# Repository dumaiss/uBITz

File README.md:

# uBITz
**μBITz** – *ZAP 80s dreams into silicon.*   

Open modular 8-bit style system: host Z80/6502/68k/RISC-V, tile SID/POKEY, boot in '83.   M.2 LVDS serial, I²C map, Parity-10, ZAP IRQs.   Spec + KiCad + Verilog + ref impl.   Build. ZAP. Retro lives.   `ubitz.dev` #μBITz

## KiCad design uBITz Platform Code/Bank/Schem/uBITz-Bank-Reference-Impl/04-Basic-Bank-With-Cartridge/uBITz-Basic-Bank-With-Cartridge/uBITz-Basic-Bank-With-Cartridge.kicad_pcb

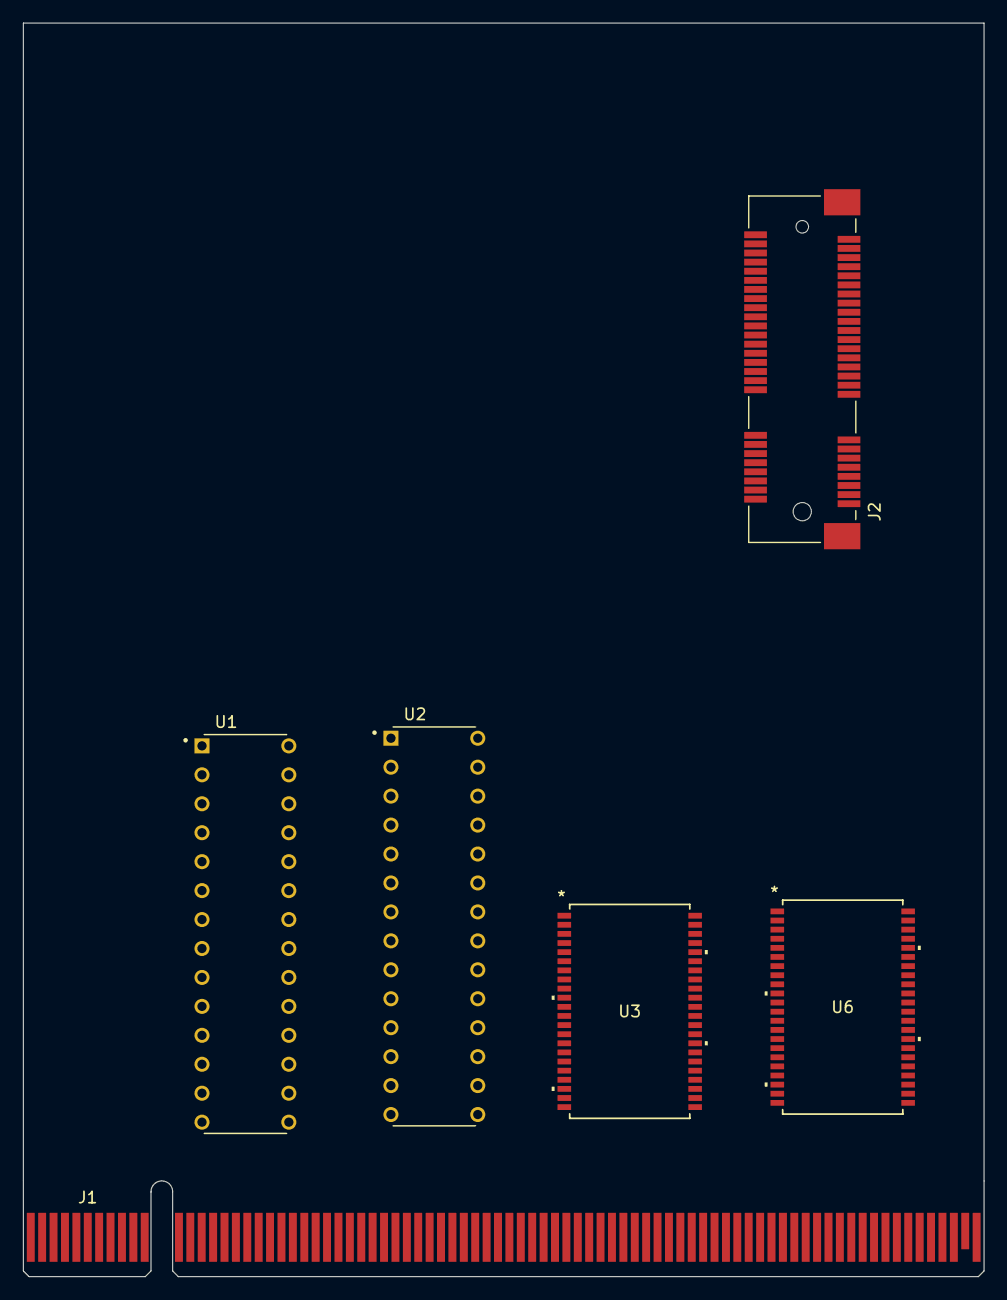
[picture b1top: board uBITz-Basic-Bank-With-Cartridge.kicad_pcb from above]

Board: 4 copper layers, 84.3 x 110.0 mm, 6 parts (0 on the bottom side), 37 nets, no tracks yet.

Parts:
J1: BUS_PCIexpress_x16
J2: uBITz-Bank-Cartridge; BUS_PCI_Express_Mini_Full
U1, U2: AT28C256-15PU; DIP762W48P254L3467H406Q28
U3, U6: AS7C34096A-10TIN; TSOP-44_18P52X11P94_ALL

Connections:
+5V: J1.A2 (+5V_MAIN), J1.A3 (+5V_MAIN), J1.B1 (+5V_MAIN), J1.B2 (+5V_MAIN), J1.B3 (+5V_MAIN), U1.28 (VCC), U2.28 (VCC), U3.11 (VCC), U3.33 (VCC), U6.11 (VCC), U6.33 (VCC)
/A0: J1.B14 (A0), U1.10 (A0), U2.10 (A0), U3.3 (A0), U6.3 (A0)
/A1: J1.B15 (A1), U1.9 (A1), U2.9 (A1), U3.4 (A1), U6.4 (A1)
/A2: J1.B17 (A2), U1.8 (A2), U2.8 (A2), U3.5 (A2), U6.5 (A2)
/A3: J1.B18 (A3), U1.7 (A3), U2.7 (A3), U3.6 (A3), U6.6 (A3)
/A4: J1.B19 (A4), U1.6 (A4), U2.6 (A4), U3.7 (A4), U6.7 (A4)
/A5: J1.B20 (A5), U1.5 (A5), U2.5 (A5), U3.16 (A5), U6.16 (A5)
/A6: J1.B23 (A6), U1.4 (A6), U2.4 (A6), U3.17 (A6), U6.17 (A6)
/A7: J1.B24 (A7), U1.3 (A7), U2.3 (A7), U3.18 (A7), U6.18 (A7)
/A8: J1.B27 (A8), U1.25 (A8), U2.25 (A8), U3.19 (A8), U6.19 (A8)
/A9: J1.B28 (A9), U1.24 (A9), U2.24 (A9), U3.20 (A9), U6.20 (A9)
/A10: J1.B30 (A10), U1.21 (A10), U2.21 (A10), U3.26 (A10), U6.26 (A10)
/A11: J1.B31 (A11), U1.23 (A11), U2.23 (A11), U3.27 (A11), U6.27 (A11)
/A12: J1.B33 (A12), U1.2 (A12), U2.2 (A12), U3.28 (A12), U6.28 (A12)
/A13: J1.B34 (A13), U1.26 (A13), U2.26 (A13), U3.29 (A13), U6.29 (A13)
/A14: J1.B37 (A14), U1.1 (A14), U2.1 (A14), U3.30 (A14), U6.30 (A14)
/A15: J1.B38 (A15), U3.38 (A15), U6.38 (A15)
/A16: J1.B41 (A16), U3.39 (A16), U6.39 (A16)
/A17: J1.B42 (A17), U3.40 (A17), U6.40 (A17)
/A18: J1.B45 (A18), U3.41 (A18), U6.41 (A18)
/D0: J1.A72 (D0), U2.11 (I/O0), U6.9 (I/O1)
/D1: J1.A69 (D1), U2.12 (I/O1), U6.10 (I/O2)
/D2: J1.A68 (D2), U2.13 (I/O2), U6.13 (I/O3)
/D3: J1.A65 (D3), U2.15 (I/O3), U6.14 (I/O4)
/D4: J1.A64 (D4), U2.19 (I/O7), U6.31 (I/O5)
/D5: J1.A61 (D5), U2.18 (I/O6), U6.32 (I/O6)
/D6: J1.A60 (D6), U2.17 (I/O5), U6.35 (I/O7)
/D7: J1.A57 (D7), U2.16 (I/O4), U6.36 (I/O8)
/D8: U1.11 (I/O0), U3.9 (I/O1)
/D9: U1.12 (I/O1), U3.10 (I/O2)
/D10: U1.13 (I/O2), U3.13 (I/O3)
/D11: U1.15 (I/O3), U3.14 (I/O4)
/D12: U1.19 (I/O7), U3.31 (I/O5)
/D13: U1.18 (I/O6), U3.32 (I/O6)
/D14: U1.17 (I/O5), U3.35 (I/O7)
/D15: U1.16 (I/O4), U3.36 (I/O8)
GND: J1.A1 (~DRV5V), J1.A4 (GND), J1.A5 (GND), J1.A6 (GND), J1.A11 (~SENS3V), J1.A12 (GND), J1.A15 (GND), J1.A18 (GND), J1.A23 (GND), J1.A24 (GND), J1.A27 (GND), J1.A28 (GND), J1.A30 (GND), J1.A34 (GND), J1.A37 (GND), J1.A38 (GND), J1.A41 (GND), J1.A42 (GND), J1.A45 (GND), J1.A46 (GND), J1.A50 (GND), J1.A51 (GND), J1.A54 (GND), J1.A55 (GND), J1.A58 (GND), J1.A59 (GND), J1.A62 (GND), J1.A63 (GND), J1.A66 (GND), J1.A67 (GND), J1.A70 (GND), J1.A71 (GND), J1.B4 (GND), J1.B7 (GND), J1.B8 (GND), J1.B11 (GND), J1.B13 (GND), J1.B16 (GND), J1.B21 (GND), J1.B22 (GND), J1.B25 (GND), J1.B26 (GND), J1.B29 (GND), J1.B32 (GND), J1.B35 (GND), J1.B36 (GND), J1.B39 (GND), J1.B40 (GND), J1.B43 (GND), J1.B44 (GND), J1.B47 (GND), J1.B48 (GND), J1.B52 (GND), J1.B53 (GND), J1.B56 (GND), J1.B57 (GND), J1.B60 (GND), J1.B61 (GND), J1.B64 (GND), J1.B65 (GND), J1.B68 (GND), J1.B69 (GND), J1.B72 (GND), U1.14 (GND), U2.14 (GND), U3.12 (GND), U3.34 (GND), U6.12 (GND), U6.34 (GND)

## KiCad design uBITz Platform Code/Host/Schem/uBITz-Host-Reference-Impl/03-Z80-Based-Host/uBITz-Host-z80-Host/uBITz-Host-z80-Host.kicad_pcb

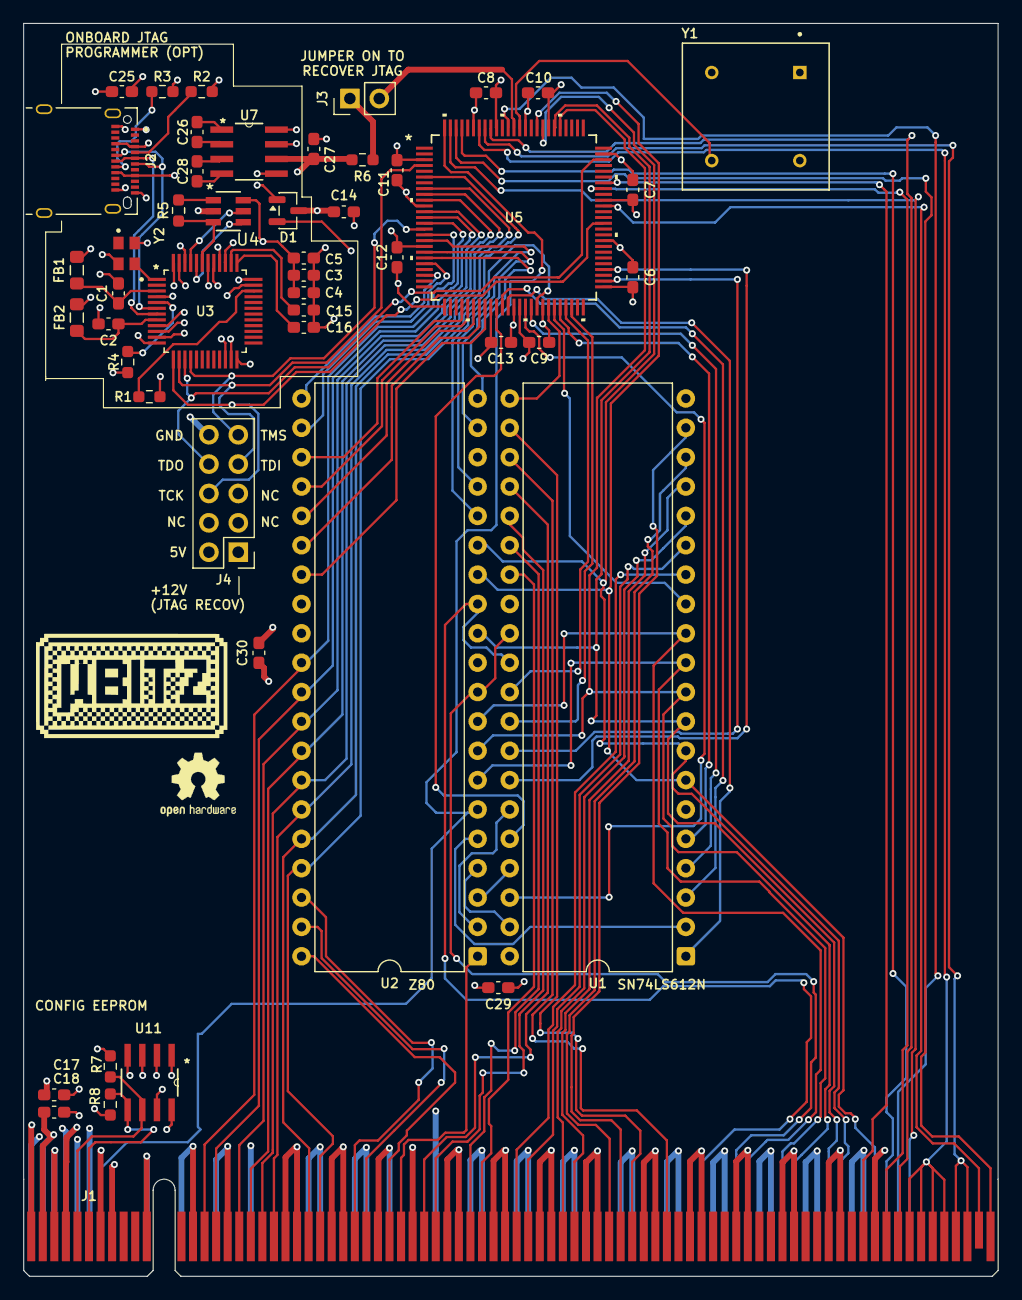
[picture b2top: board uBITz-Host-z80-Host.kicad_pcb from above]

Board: 4 copper layers, 84.3 x 108.4 mm, 48 parts (0 on the bottom side), 104 nets.

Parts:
C1, C2, C3, C14, C17, C18: 10u; C_0603_1608Metric_Pad1.08x0.95mm_HandSolder
C4, C5, C15, C16: 1000n; C_0603_1608Metric_Pad1.08x0.95mm_HandSolder
C6, C7, C8, C9, C10, C11, C12, C13, C29, C30: 100n; C_0603_1608Metric_Pad1.08x0.95mm_HandSolder
C25: 2u; C_0603_1608Metric_Pad1.08x0.95mm_HandSolder
C26, C28: 220n; C_0603_1608Metric_Pad1.08x0.95mm_HandSolder
C27: 1u; C_0603_1608Metric_Pad1.08x0.95mm_HandSolder
D1: BAT54C; SOT-23
FB1, FB2: 600R/500mA; L_0805_2012Metric_Pad1.05x1.20mm_HandSolder
J1: BUS_PCIexpress_x16
J2: 12401610E4_2A; AMPHENOL_12401610E4_2A
J3: Conn_01x02_Pin; PinHeader_1x02_P2.54mm_Vertical
J4: Conn_02x05_Top_Bottom; PinHeader_2x05_P2.54mm_Vertical
R1, R4: 12k; R_0603_1608Metric_Pad0.98x0.95mm_HandSolder
R2, R3: 5k1; R_0603_1608Metric_Pad0.98x0.95mm_HandSolder
R5, R6, R7, R8: 2k2; R_0603_1608Metric_Pad0.98x0.95mm_HandSolder
U1: SN74LS612N; DIP-40_W15.24mm
U2: Z084000xP; DIP-40_W15.24mm
U3: FT232HL; QFP50P900X900X160-48N
U4: 93LC56BT-I/OT; SOT-23-6_MC_MCH
U5: ATF1504AS-10AU100; 100A_ATM
U7: MAX662ACSA_T; SOIC127P600X175-8N
U11: 24LC16BT-I_SN; SOIC127P600X175-8N
Y1: ACH-14.31818MHZ-EK; XTAL_ACH-14.31818MHZ-EK
Y2: ECS-2033-120-BN; OSC_ECS-2033-120-BN

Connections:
+5V: C17.1, C18.1, C29.1, C30.1, D1.2, J1.A2 (+5V_MAIN), J1.A3 (+5V_MAIN), J1.B1 (+5V_MAIN), J1.B2 (+5V_MAIN), J1.B3 (+5V_MAIN), R7.1, R8.2, U1.40 (VCC), U2.11 (V_{CC}), U11.8 (VCC), Y1.8 (VDD)
+5V_CPLD: C6.1, C7.1, C8.1, C9.1, C10.1, C11.1, C12.1, C13.1, C14.1, D1.3, J4.2, U5.3 (VCCIO), U5.18 (VCCIO), U5.34 (VCCIO), U5.39 (VCCINT), U5.51 (VCCIO), U5.66 (VCCIO), U5.82 (VCCIO), U5.91 (VCCINT)
+5V_VBUS: C25.1, D1.1, J2.A4 (VBUS_A), J2.A9 (VBUS_A__1), J2.B4 (VBUS_B), J2.B9 (VBUS_B__1), U3.40 (VREGIN), U7.5 (VCC)
+12V: C27.1, J4.1, R6.2, U7.6 (VOUT)
/A0: J1.B14 (A0), U2.30 (A_{0}), U5.16 (I/O)
/A1: J1.B15 (A1), U2.31 (A_{1}), U5.14 (I/O)
/A2: J1.B17 (A2), U2.32 (A_{2}), U5.13 (I/O)
/A3: J1.B18 (A3), U2.33 (A_{3}), U5.12 (I/O/PD1)
/A4: J1.B19 (A4), U2.34 (A_{4}), U5.10 (I/O)
/A5: J1.B20 (A5), U2.35 (A_{5}), U5.9 (I/O)
/A6: J1.B23 (A6), U2.36 (A_{6}), U5.8 (I/O)
/A7: J1.B24 (A7), U2.37 (A_{7}), U5.6 (I/O)
/A8: J1.B27 (A8), U2.38 (A_{8})
/A9: J1.B28 (A9), U2.39 (A_{9})
/A10: J1.B30 (A10), U2.40 (A_{10})
/A11: J1.B31 (A11), U2.1 (A_{11})
/A12: J1.B33 (A12), U1.24 (MO8)
/A13: J1.B34 (A13), U1.25 (MO9)
/A14: J1.B37 (A14), U1.26 (MO10)
/A15: J1.B38 (A15), U1.27 (MO11)
/A16: J1.B41 (A16), U1.14 (MO0)
/A17: J1.B42 (A17), U1.15 (MO1)
/A18: J1.B45 (A18), U1.16 (MO2)
/A19: J1.B46 (A19), U1.17 (MO3)
/A20: J1.B49 (A20), U1.18 (MO4)
/A21: J1.B50 (A21), U1.19 (MO5)
/A22: J1.B51 (A22), U1.22 (MO6)
/A23: J1.B54 (A23), U1.23 (MO7)
/BUS_R/~W: J1.A75 (R/~W), U5.99 (I/O)
/BUS_SCL: J1.B5 (SLOT_SCL), R7.2, U11.6 (SCL)
/BUS_SDA: J1.B6 (SLOT_SDA), R8.1, U11.5 (SDA)
/CLK: U5.87 (INPUT/GCLK1), Y1.5 (OUTPUT)
/CPUCLK: J1.A7 (CLK_HOST), U2.6 (CLK), U5.100 (I/O)
/D0: J1.A72 (D0), U1.7 (D0), U2.14 (D_{0}), U5.84 (I/O)
/D1: J1.A69 (D1), U1.8 (D1), U2.15 (D_{1}), U5.83 (I/O)
/D2: J1.A68 (D2), U1.9 (D2), U2.12 (D_{2}), U5.81 (I/O)
/D3: J1.A65 (D3), U1.10 (D3), U2.8 (D_{3}), U5.80 (I/O)
/D4: J1.A64 (D4), U1.11 (D4), U2.7 (D_{4})
/D5: J1.A61 (D5), U1.12 (D5), U2.9 (D_{5})
/D6: J1.A60 (D6), U1.29 (D6), U2.10 (D_{6})
/D7: J1.A57 (D7), U1.30 (D7), U2.13 (D_{7})
/D+: J2.A6 (D1+), J2.B6 (D2+), U3.7 (DP)
/D-: J2.A7 (D1-), J2.B7 (D2-), U3.6 (DM)
/EECLK: U3.44 (EECLK), U4.4 (CLK)
/EECS: U3.45 (EECS), U4.5 (CS)
/EEDATA: R5.2, U3.43 (EEDATA), U4.3 (DI)
/MA0: U1.35 (MA0), U2.2 (A_{12})
/MA1: U1.37 (MA1), U2.3 (A_{13})
/MA2: U1.39 (MA2), U2.4 (A_{14})
/MA3: U1.2 (MA3), U2.5 (A_{15})
/MAP_D8: U1.31 (D8), U5.47 (I/O)
/MAP_D9: U1.32 (D9), U5.48 (I/O)
/MAP_D10: U1.33 (D10), U5.52 (I/O)
/MAP_D11: U1.34 (D11), U5.54 (I/O)
/MAP_RS0: U1.36 (RS0), U5.35 (I/O)
/MAP_RS1: U1.38 (RS1), U5.40 (I/O)
/MAP_RS2: U1.1 (RS2), U5.37 (I/O)
/MAP_RS3: U1.3 (RS3), U5.36 (I/O)
/MAP_~CS: U1.4 (~CS), U5.41 (I/O)
/MAP_~ME: U1.21 (~ME), U5.44 (I/O)
/MAP_~MM: U1.13 (~MM), U5.45 (I/O)
/MAP_~STROBE: U1.5 (~STROBE), U5.46 (I/O)
/RECOV: J3.2, U5.88 (INPUT/OE1)
/TCK: J4.6, U3.13 (ADBUS0), U5.62 (I/O/TCK)
/TDI: J4.7, U3.14 (ADBUS1), U5.4 (I/O/TDI)
/TDO: J4.8, U3.15 (ADBUS2), U5.73 (I/O/TDO)
/TMS: J4.9, U3.16 (ADBUS3), U5.15 (I/O/TMS)
/XCSI: U3.1 (XCSI), Y2.3 (OUT)
/~BUSACK: U2.23 (~BUSACK), U5.29 (I/O)
/~BUSREQ: U2.25 (~BUSREQ), U5.31 (I/O)
/~BUS_CPU_ACK: J1.B74 (~CPU_ACK), U5.92 (I/O)
/~BUS_CPU_INT: J1.B75 (~CPU_INT0), J1.B76 (~CPU_INT1), J1.B77 (~CPU_INT2), J1.B78 (~CPU_INT3), U5.94 (I/O)
/~BUS_CPU_NMI: J1.B79 (~CPU_NMI0), J1.B80 (~CPU_NMI1), U5.93 (I/O)
/~BUS_DMA_GNT: J1.B73 (~DMA_GNT), U5.68 (I/O)
/~BUS_DMA_REQ: J1.B71 (~DMA_REQ), U5.69 (I/O)
/~BUS_IORQ: J1.B82 (~IORQ), U5.98 (I/O)
/~BUS_MREQ: J1.B81 (~MREQ), U5.65 (I/O)
/~BUS_READY: J1.A73 (~READY), U5.97 (I/O)
/~BUS_RESET: J1.A74 (~RESET), U5.89 (INPUT/GCLR)
/~INT: U2.16 (~INT), U5.42 (I/O/PD2)
/~IORQ: U2.20 (~IORQ), U5.20 (I/O)
/~M1: U2.27 (~M1), U5.33 (I/O)
/~MREQ: U2.19 (~MREQ), U5.19 (I/O)
/~NMI: U2.17 (~NMI), U5.17 (I/O)
/~RD: U2.21 (~RD), U5.23 (I/O)
/~RESET: U2.26 (~RESET), U5.32 (I/O)
/~WAIT: U2.24 (~WAIT), U5.30 (I/O)
/~WR: U2.22 (~WR), U5.21 (I/O)
GND: C1.2, C2.2, C3.2, C4.2, C5.2, C6.2, C7.2, C8.2, C9.2, C10.2, C11.2, C12.2, C13.2, C14.2, C15.2, C16.2, C17.2, C18.2, C25.2, C27.2, C29.2, C30.2, J1.A1 (~VIO_5V), J1.A4 (GND), J1.A5 (GND), J1.A6 (GND), J1.A11 (~SLOT_PRSNT), J1.A12 (GND), J1.A15 (GND), J1.A18 (GND), J1.A23 (GND), J1.A24 (GND), J1.A27 (GND), J1.A28 (GND), J1.A30 (GND), J1.A34 (GND), J1.A37 (GND), J1.A38 (GND), J1.A41 (GND), J1.A42 (GND), J1.A45 (GND), J1.A46 (GND), J1.A50 (GND), J1.A51 (GND), J1.A54 (GND), J1.A55 (GND), J1.A58 (GND), J1.A59 (GND), J1.A62 (GND), J1.A63 (GND), J1.A66 (GND), J1.A67 (GND), J1.A70 (GND), J1.A71 (GND), J1.B4 (GND), J1.B7 (GND), J1.B8 (GND), J1.B11 (GND), J1.B13 (GND), J1.B16 (GND), J1.B21 (GND), J1.B22 (GND), J1.B25 (GND), J1.B26 (GND), J1.B29 (GND), J1.B32 (GND), J1.B35 (GND), J1.B36 (GND), J1.B39 (GND), J1.B40 (GND), J1.B43 (GND), J1.B44 (GND), J1.B47 (GND), J1.B48 (GND), J1.B52 (GND), J1.B53 (GND), J1.B56 (GND), J1.B57 (GND), J1.B60 (GND), J1.B61 (GND), J1.B64 (GND), J1.B65 (GND), J1.B68 (GND), J1.B69 (GND), J1.B72 (GND), J2.A1 (GND_A), J2.A12 (GND_A__1), J2.B1 (GND_B), J2.B12 (GND_B__1), J2.SH1 (SHIELD), J2.SH2 (SHIELD__1), J2.SH3 (SHIELD__2), J2.SH4 (SHIELD__3), J4.10, R2.2, R3.1, R4.2, U1.6 (R/~W), U1.20 (GND), U2.29 (GND), U3.4 (AGND), U3.9 (AGND), U3.10 (GND), U3.11 (GND), U3.22 (GND), U3.23 (GND), U3.35 (GND), U3.36 (GND), U3.41 (AGND), U3.42 (TEST), U3.47 (GND), U3.48 (GND), U4.2 (VSS), U5.11 (GND), U5.26 (GND), U5.38 (GND), U5.43 (GND), U5.59 (GND), U5.74 (GND), U5.86 (GND), U5.95 (GND), U7.7 (GND), U7.8 (SHDN), U11.1 (A0), U11.2 (A1), U11.3 (A2), U11.4 (VSS), U11.7 (WP), Y1.4 (CASE_GND), Y2.2 (GND)
unnamed: J2.A5 (CC1), R2.1
unnamed: J2.B5 (CC2), R3.2
unnamed: J3.1, R6.1
unnamed: R4.1, U3.5 (REF)
unnamed: C16.1, U3.37 (VCCA)
unnamed: C15.1, U3.38 (VCCCORE)
unnamed: C1.1, FB1.1, U3.3 (VPHY)
unnamed: C2.1, FB2.2, U3.8 (VPLL)
unnamed: R1.1, U3.34 (~RESET)
unnamed: R5.1, U4.1 (DO)
unnamed: C26.1, U7.2 (C1+)
unnamed: C26.2, U7.1 (C1-)
unnamed: C28.1, U7.4 (C2+)
unnamed: C28.2, U7.3 (C2-)
VCCD: C3.1, C4.1, C5.1, FB1.2, FB2.1, R1.2, U3.12 (VCCIO), U3.24 (VCCIO), U3.39 (VCCD), U3.46 (VCCIO), U4.6 (VCC), Y2.4 (VDD)

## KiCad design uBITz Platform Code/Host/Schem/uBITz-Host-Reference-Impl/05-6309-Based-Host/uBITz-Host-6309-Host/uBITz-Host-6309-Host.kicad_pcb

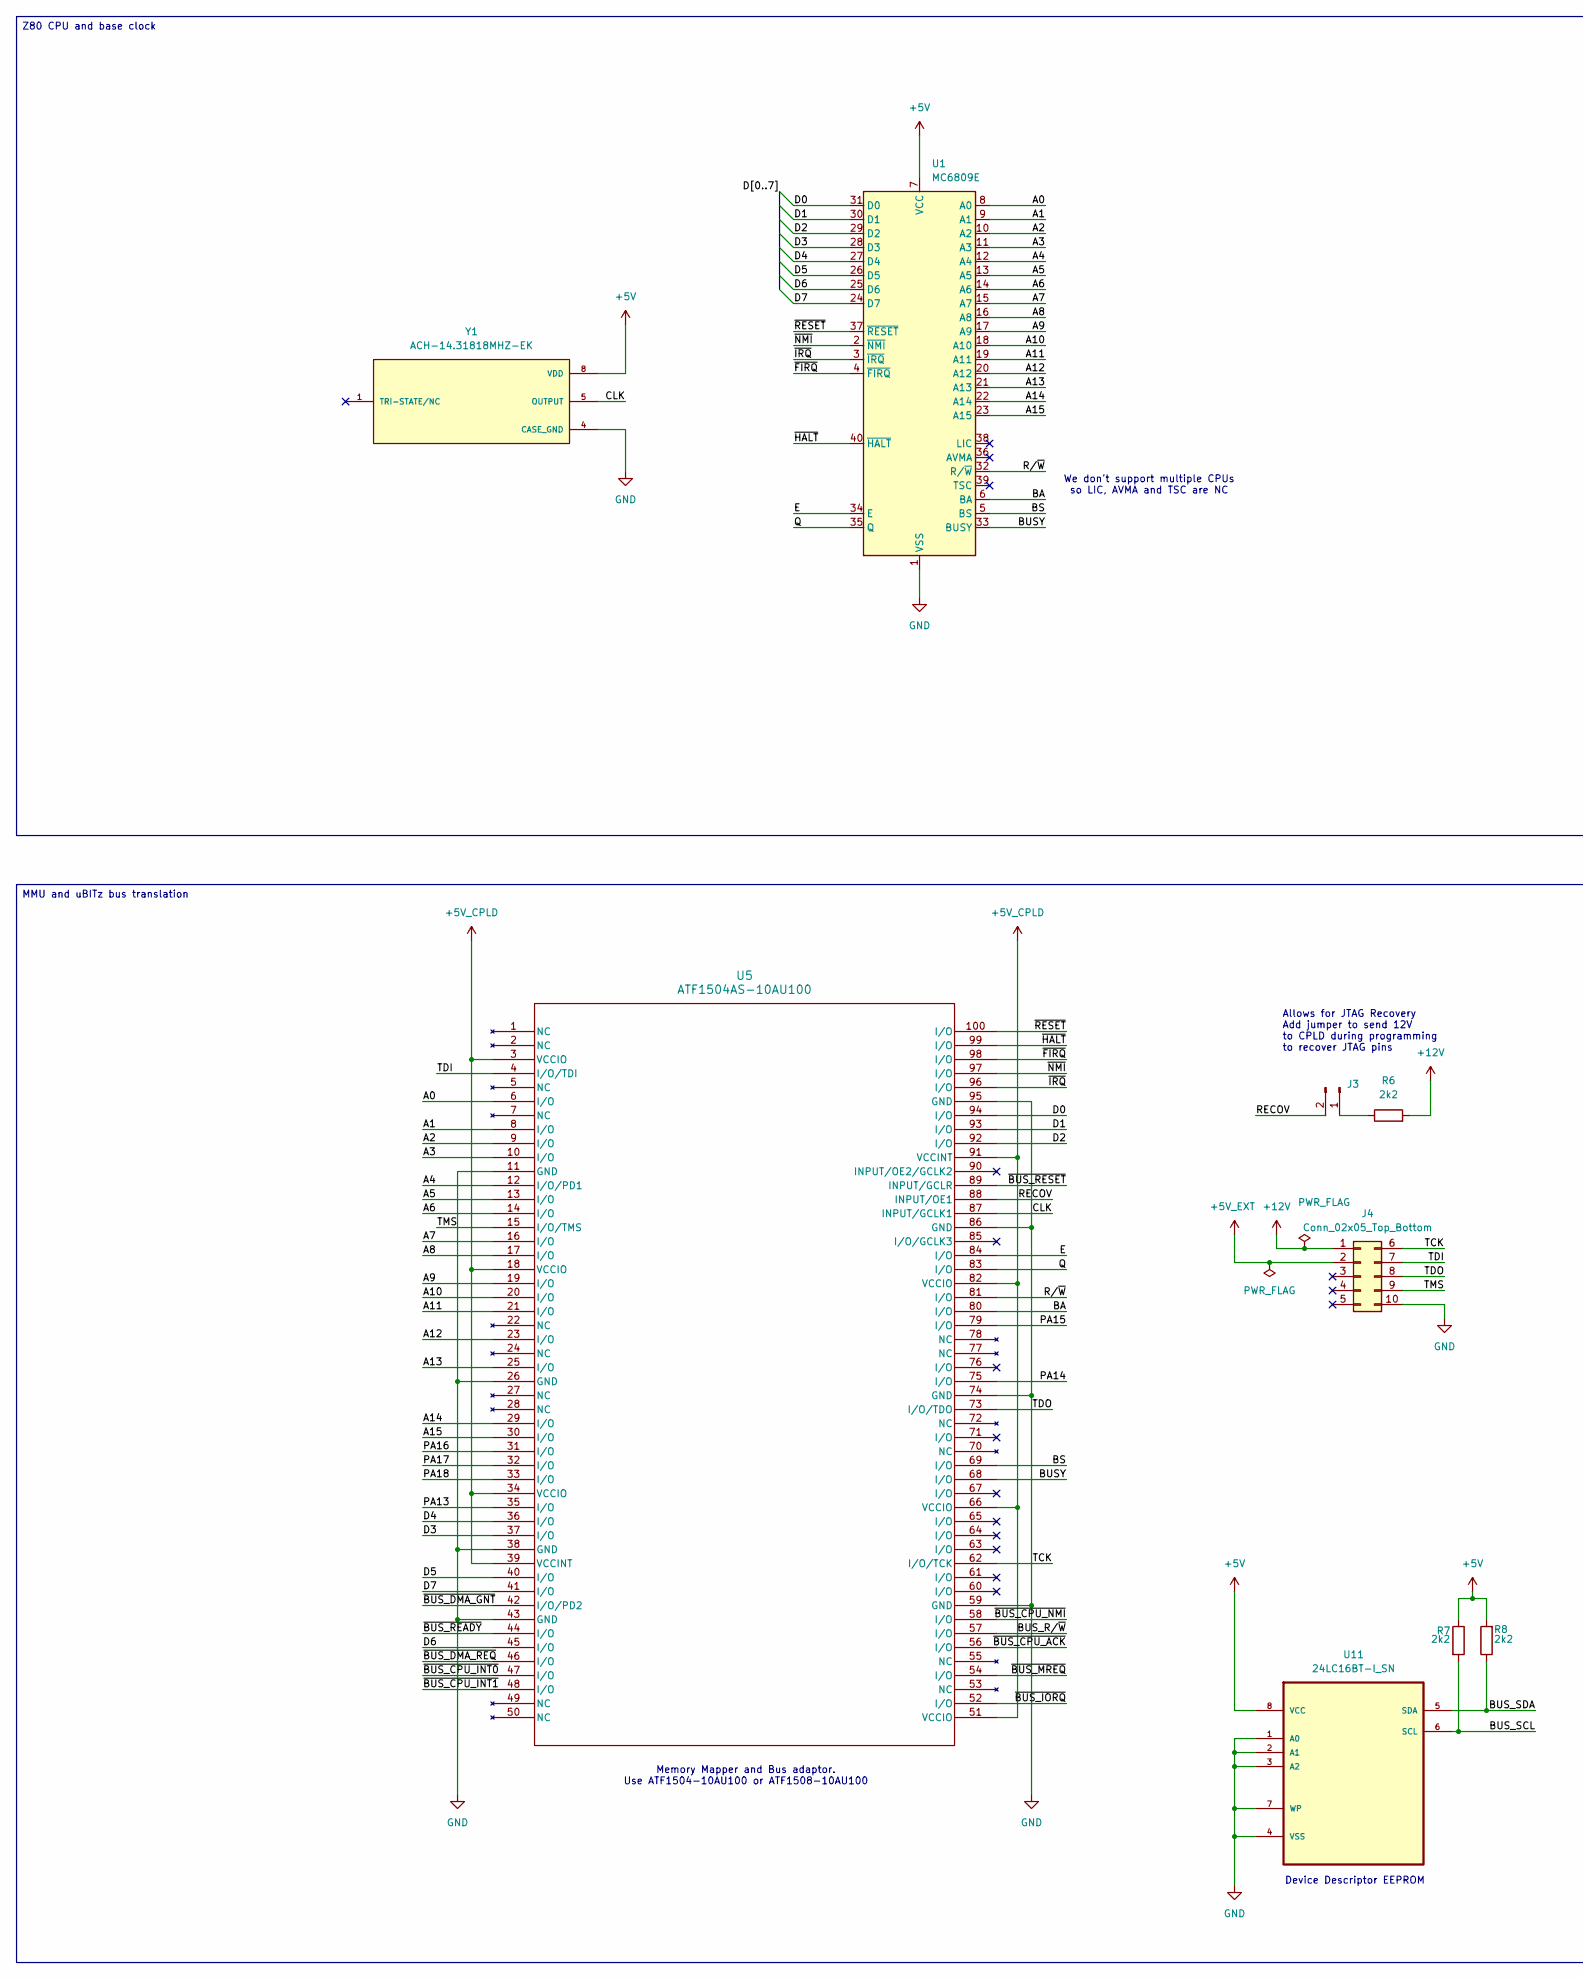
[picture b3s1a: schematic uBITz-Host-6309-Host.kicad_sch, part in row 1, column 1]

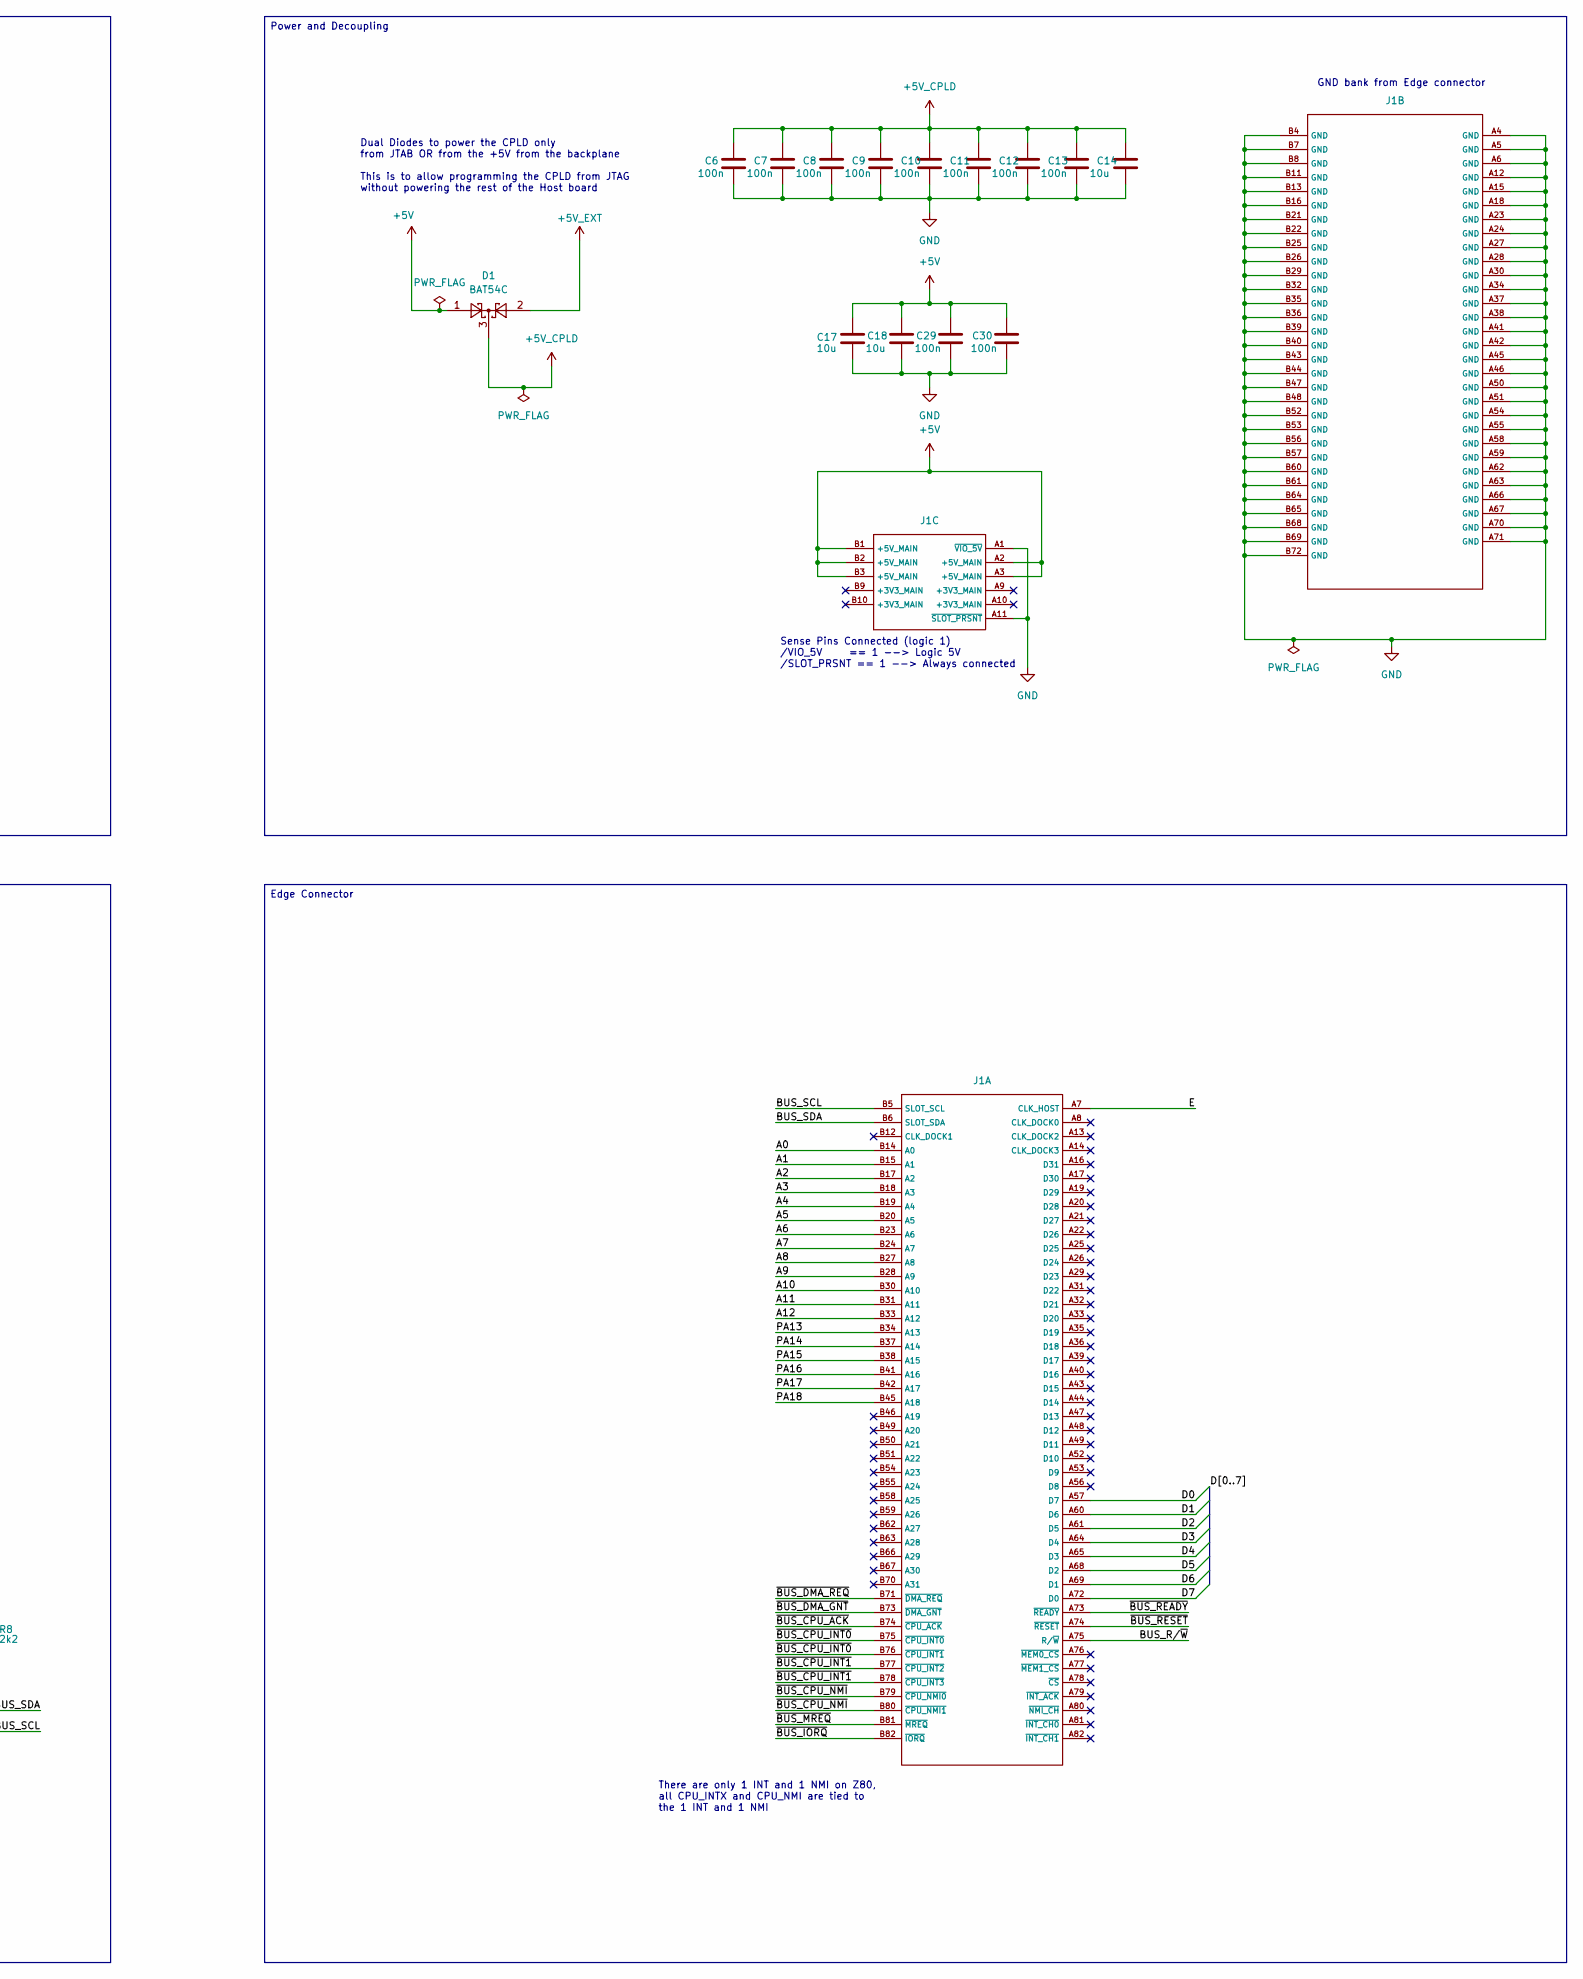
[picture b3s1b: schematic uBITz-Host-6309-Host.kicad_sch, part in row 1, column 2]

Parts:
C6, C7, C8, C9, C10, C11, C12, C13, C29, C30: 100n; C_0603_1608Metric_Pad1.08x0.95mm_HandSolder
C14, C17, C18: 10u; C_0603_1608Metric_Pad1.08x0.95mm_HandSolder
D1: BAT54C; SOT-23
J1: BUS_PCIexpress_x16
J3: Conn_01x02_Pin; PinHeader_1x02_P2.54mm_Vertical
J4: Conn_02x05_Top_Bottom; PinHeader_2x05_P2.54mm_Vertical
R6, R7, R8: 2k2; R_0603_1608Metric_Pad0.98x0.95mm_HandSolder
U1: MC6809E; DIP-40_W15.24mm
U5: ATF1504AS-10AU100; 100A_ATM
U11: 24LC16BT-I_SN; SOIC127P600X175-8N; MPN 24LC16BT-I/SN
Y1: ACH-14.31818MHZ-EK; XTAL_ACH-14.31818MHZ-EK; PARTREV 11.15.2016

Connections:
+5V: C17.1, C18.1, C29.1, C30.1, D1.1, J1.A2 (+5V_MAIN), J1.A3 (+5V_MAIN), J1.B1 (+5V_MAIN), J1.B2 (+5V_MAIN), J1.B3 (+5V_MAIN), R7.1, R8.2, U1.7 (VCC), U11.8 (VCC), Y1.8 (VDD)
+5V_CPLD: C6.1, C7.1, C8.1, C9.1, C10.1, C11.1, C12.1, C13.1, C14.1, D1.3, U5.3 (VCCIO), U5.18 (VCCIO), U5.34 (VCCIO), U5.39 (VCCINT), U5.51 (VCCIO), U5.66 (VCCIO), U5.82 (VCCIO), U5.91 (VCCINT)
+5V_EXT: D1.2, J4.2
+12V: J4.1, R6.2
/A0: J1.B14 (A0), U1.8 (A0), U5.6 (I/O)
/A1: J1.B15 (A1), U1.9 (A1), U5.8 (I/O)
/A2: J1.B17 (A2), U1.10 (A2), U5.9 (I/O)
/A3: J1.B18 (A3), U1.11 (A3), U5.10 (I/O)
/A4: J1.B19 (A4), U1.12 (A4), U5.12 (I/O/PD1)
/A5: J1.B20 (A5), U1.13 (A5), U5.13 (I/O)
/A6: J1.B23 (A6), U1.14 (A6), U5.14 (I/O)
/A7: J1.B24 (A7), U1.15 (A7), U5.16 (I/O)
/A8: J1.B27 (A8), U1.16 (A8), U5.17 (I/O)
/A9: J1.B28 (A9), U1.17 (A9), U5.19 (I/O)
/A10: J1.B30 (A10), U1.18 (A10), U5.20 (I/O)
/A11: J1.B31 (A11), U1.19 (A11), U5.21 (I/O)
/A12: J1.B33 (A12), U1.20 (A12), U5.23 (I/O)
/A13: U1.21 (A13), U5.25 (I/O)
/A14: U1.22 (A14), U5.29 (I/O)
/A15: U1.23 (A15), U5.30 (I/O)
/BA: U1.6 (BA), U5.80 (I/O)
/BS: U1.5 (BS), U5.69 (I/O)
/BUSY: U1.33 (BUSY), U5.68 (I/O)
/BUS_R/~W: J1.A75 (R/~W), U5.57 (I/O)
/BUS_SCL: J1.B5 (SLOT_SCL), R7.2, U11.6 (SCL)
/BUS_SDA: J1.B6 (SLOT_SDA), R8.1, U11.5 (SDA)
/CLK: U5.87 (INPUT/GCLK1), Y1.5 (OUTPUT)
/D0: J1.A57 (D7), U1.31 (D0), U5.94 (I/O)
/D1: J1.A60 (D6), U1.30 (D1), U5.93 (I/O)
/D2: J1.A61 (D5), U1.29 (D2), U5.92 (I/O)
/D3: J1.A64 (D4), U1.28 (D3), U5.37 (I/O)
/D4: J1.A65 (D3), U1.27 (D4), U5.36 (I/O)
/D5: J1.A68 (D2), U1.26 (D5), U5.40 (I/O)
/D6: J1.A69 (D1), U1.25 (D6), U5.45 (I/O)
/D7: J1.A72 (D0), U1.24 (D7), U5.41 (I/O)
/E: J1.A7 (CLK_HOST), U1.34 (E), U5.84 (I/O)
/PA13: J1.B34 (A13), U5.35 (I/O)
/PA14: J1.B37 (A14), U5.75 (I/O)
/PA15: J1.B38 (A15), U5.79 (I/O)
/PA16: J1.B41 (A16), U5.31 (I/O)
/PA17: J1.B42 (A17), U5.32 (I/O)
/PA18: J1.B45 (A18), U5.33 (I/O)
/Q: U1.35 (Q), U5.83 (I/O)
/RECOV: J3.2, U5.88 (INPUT/OE1)
/R/~W: U1.32 (R/~W), U5.81 (I/O)
/TCK: J4.6, U5.62 (I/O/TCK)
/TDI: J4.7, U5.4 (I/O/TDI)
/TDO: J4.8, U5.73 (I/O/TDO)
/TMS: J4.9, U5.15 (I/O/TMS)
/~BUS_CPU_ACK: J1.B74 (~CPU_ACK), U5.56 (I/O)
/~BUS_CPU_INT0: J1.B75 (~CPU_INT0), J1.B76 (~CPU_INT1), U5.47 (I/O)
/~BUS_CPU_INT1: J1.B77 (~CPU_INT2), J1.B78 (~CPU_INT3), U5.48 (I/O)
/~BUS_CPU_NMI: J1.B79 (~CPU_NMI0), J1.B80 (~CPU_NMI1), U5.58 (I/O)
/~BUS_DMA_GNT: J1.B73 (~DMA_GNT), U5.42 (I/O/PD2)
/~BUS_DMA_REQ: J1.B71 (~DMA_REQ), U5.46 (I/O)
/~BUS_IORQ: J1.B82 (~IORQ), U5.52 (I/O)
/~BUS_MREQ: J1.B81 (~MREQ), U5.54 (I/O)
/~BUS_READY: J1.A73 (~READY), U5.44 (I/O)
/~BUS_RESET: J1.A74 (~RESET), U5.89 (INPUT/GCLR)
/~FIRQ: U1.4 (~FIRQ), U5.98 (I/O)
/~HALT: U1.40 (~HALT), U5.99 (I/O)
/~IRQ: U1.3 (~IRQ), U5.96 (I/O)
/~NMI: U1.2 (~NMI), U5.97 (I/O)
/~RESET: U1.37 (~RESET), U5.100 (I/O)
GND: C6.2, C7.2, C8.2, C9.2, C10.2, C11.2, C12.2, C13.2, C14.2, C17.2, C18.2, C29.2, C30.2, J1.A1 (~VIO_5V), J1.A4 (GND), J1.A5 (GND), J1.A6 (GND), J1.A11 (~SLOT_PRSNT), J1.A12 (GND), J1.A15 (GND), J1.A18 (GND), J1.A23 (GND), J1.A24 (GND), J1.A27 (GND), J1.A28 (GND), J1.A30 (GND), J1.A34 (GND), J1.A37 (GND), J1.A38 (GND), J1.A41 (GND), J1.A42 (GND), J1.A45 (GND), J1.A46 (GND), J1.A50 (GND), J1.A51 (GND), J1.A54 (GND), J1.A55 (GND), J1.A58 (GND), J1.A59 (GND), J1.A62 (GND), J1.A63 (GND), J1.A66 (GND), J1.A67 (GND), J1.A70 (GND), J1.A71 (GND), J1.B4 (GND), J1.B7 (GND), J1.B8 (GND), J1.B11 (GND), J1.B13 (GND), J1.B16 (GND), J1.B21 (GND), J1.B22 (GND), J1.B25 (GND), J1.B26 (GND), J1.B29 (GND), J1.B32 (GND), J1.B35 (GND), J1.B36 (GND), J1.B39 (GND), J1.B40 (GND), J1.B43 (GND), J1.B44 (GND), J1.B47 (GND), J1.B48 (GND), J1.B52 (GND), J1.B53 (GND), J1.B56 (GND), J1.B57 (GND), J1.B60 (GND), J1.B61 (GND), J1.B64 (GND), J1.B65 (GND), J1.B68 (GND), J1.B69 (GND), J1.B72 (GND), J4.10, U1.1 (VSS), U5.11 (GND), U5.26 (GND), U5.38 (GND), U5.43 (GND), U5.59 (GND), U5.74 (GND), U5.86 (GND), U5.95 (GND), U11.1 (A0), U11.2 (A1), U11.3 (A2), U11.4 (VSS), U11.7 (WP), Y1.4 (CASE_GND)
unnamed: J3.1, R6.1

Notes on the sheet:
Memory Mapper and Bus adaptor. Use ATF1504-10AU100 or ATF1508-10AU100
GND bank from Edge connector
Sense Pins Connected (logic 1) /VIO_5V == 1 --> Logic 5V /SLOT_PRSNT == 1 --> Always connected
There are only 1 INT and 1 NMI on Z80, all CPU_INTX and CPU_NMI are tied to the 1 INT and 1 NMI
Dual Diodes to power the CPLD only from JTAB OR from the +5V from the backplane This is to allow programming the CPLD from JTAG without powering the rest of the Host board
We don't support multiple CPUs so LIC, AVMA and TSC are NC
Device Descriptor EEPROM
Allows for JTAG Recovery Add jumper to send 12V to CPLD during programming to recover JTAG pins
Power and Decoupling
MMU and uBITz bus translation
Z80 CPU and base clock
Edge Connector

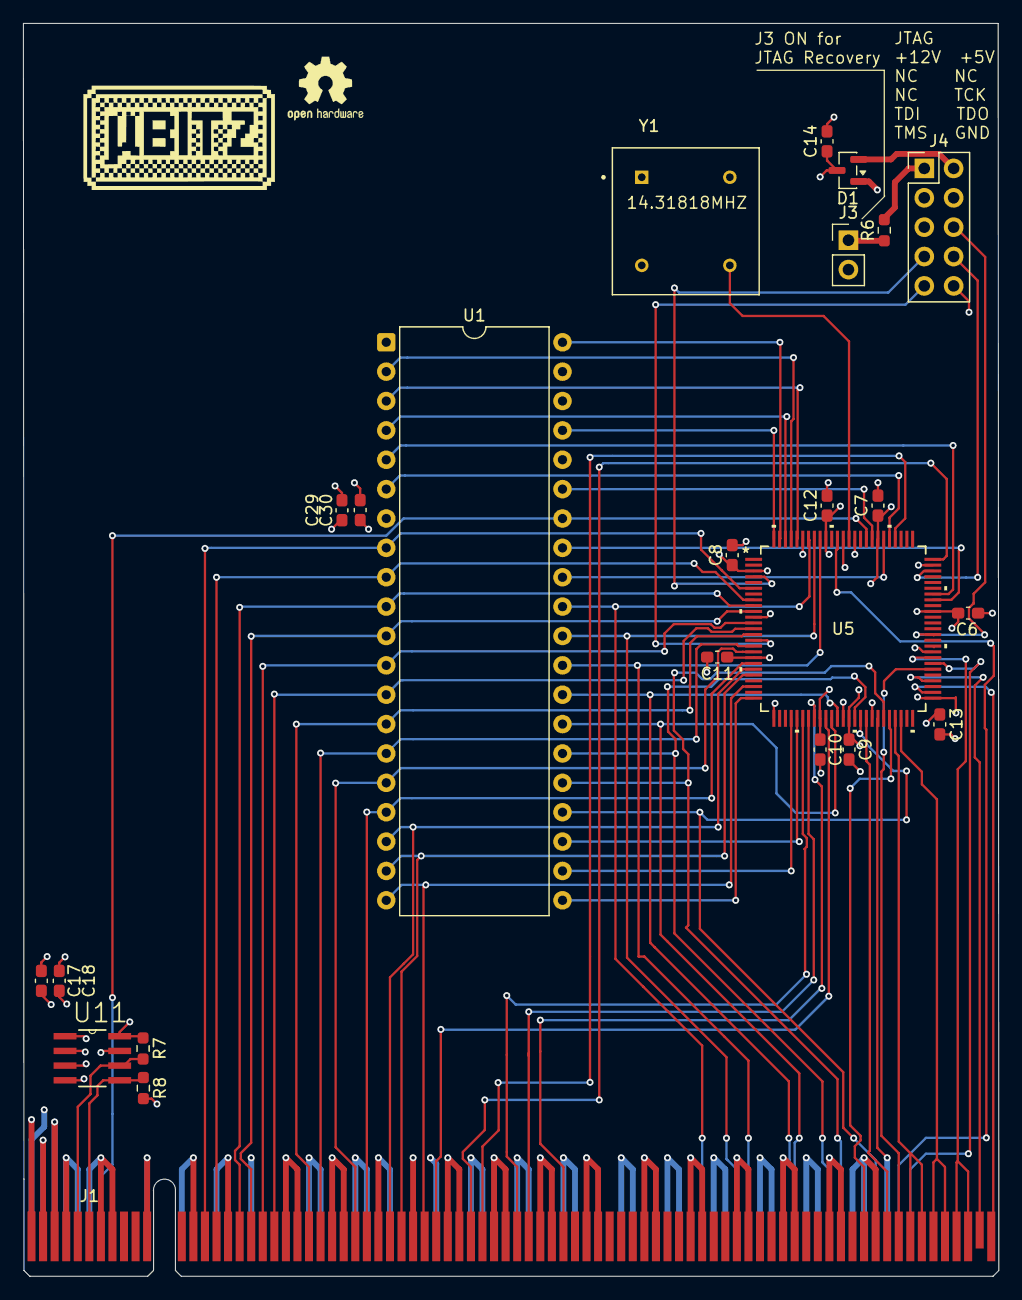
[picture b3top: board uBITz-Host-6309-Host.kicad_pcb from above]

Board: 4 copper layers, 84.3 x 108.3 mm, 24 parts (0 on the bottom side), 66 nets.
